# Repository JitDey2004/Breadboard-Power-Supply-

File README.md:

# Breadboard Power Supply

This project is a simple breadboard power supply PCB made in KiCad. It is designed to take a DC input supply and provide useful output rails for breadboard experiments.

The board includes a barrel jack input, an on/off slide switch, voltage regulators, output headers, screw terminals, and a power indicator LED. The schematic uses a 12 V input label, a fixed 5 V regulator, and an LM317 regulator set up for a 3.3 V output.

## What This Board Does

- Accepts power through a DC barrel jack.
- Uses a slide switch to turn the board on and off.
- Provides a regulated 5 V output using an LM7805 regulator.
- Provides a regulated 3.3 V output using an LM317 regulator.
- Breaks out power through pin headers and screw terminals.
- Shows power status with an LED indicator.

This kind of board is useful when testing small circuits on a breadboard. It lets you power logic circuits, sensors, microcontrollers, and other low-voltage modules from one compact PCB.

## Project Files

| File | Purpose |
| --- | --- |
| `Breadboard Power Supply.kicad_pro` | Main KiCad project file. Open this file in KiCad. |
| `Breadboard Power Supply.kicad_sch` | Schematic file. This shows the electrical circuit. |
| `Breadboard Power Supply.kicad_pcb` | PCB layout file. This shows the board routing and component placement. |
| `Breadboard Power Supply.kicad_prl` | KiCad local project settings file. |
| `0398800302.stp` | 3D model used by the PCB. |
| `500SSP1S1M2REA--3DModel-STEP-418109.STEP` | 3D model used by the PCB. |
| `img/` | Photos shown in this README. |
| `Breadboard Power Supply-backups/` | KiCad backup files. |

## Main Components

The schematic includes these main parts:

- `J1`: DC barrel jack input.
- `S1`: EG1218 slide switch.
- `U2`: LM7805 regulator for the 5 V rail.
- `U1`: LM317 regulator for the 3.3 V rail.
- `D1`: Power indicator LED.
- `R1`, `R2`, `R3`: Resistors for LED current limiting and regulator setting.
- `C1`, `C2`, `C3`: Capacitors for regulator stability and filtering.
- `J2`, `J5`: Screw terminal outputs.
- `J3`, `J4`, `J6`, `J7`: Pin header outputs.

## Power Notes

The input net is labelled as `12V` in the schematic. Use a DC supply that is suitable for the regulators and the parts installed on the board.

The LM7805 regulator creates the 5 V output. The LM317 regulator creates the 3.3 V output using the resistor values shown in the schematic.

Linear regulators can become hot when the input voltage is much higher than the output voltage or when the load current is high. Check the regulator temperature during testing. Add heatsinks if needed.

## How to Open the Project

1. Install KiCad.
2. Open KiCad.
3. Choose **File > Open Project**.
4. Select `Breadboard Power Supply.kicad_pro`.
5. Open the schematic or PCB layout from the KiCad project window.

## Before Making the PCB

Before sending the board for manufacturing, check the design carefully:

1. Run the Electrical Rules Checker in the schematic editor.
2. Run the Design Rules Checker in the PCB editor.
3. Confirm the footprints match the real parts you will use.
4. Check the pinout of the barrel jack, regulators, switch, headers, and screw terminals.
5. Inspect the 3D view to make sure the parts fit correctly.
6. Generate Gerber files only after the checks pass.

## Suggested Assembly Order

1. Solder the resistors first.
2. Solder the capacitors.
3. Solder the LED.
4. Solder the pin headers and screw terminals.
5. Solder the barrel jack and slide switch.
6. Solder the voltage regulators last.
7. Inspect all solder joints before applying power.

## First Power Test

Use a current-limited power supply for the first test if possible.

1. Keep the board disconnected from any breadboard circuit.
2. Apply the input voltage.
3. Turn the slide switch on.
4. Check that the power LED turns on.
5. Measure the 5 V output with a multimeter.
6. Measure the 3.3 V output with a multimeter.
7. Turn the board off and check that the outputs turn off.

Do not connect sensitive parts until the output voltages are confirmed.

## Safety

This board is intended for low-voltage electronics experiments. Do not connect it directly to mains voltage. Always check polarity before applying power.

## Author

Designed by Jit Dey.

## Project Images

These photos show the breadboard power supply project.

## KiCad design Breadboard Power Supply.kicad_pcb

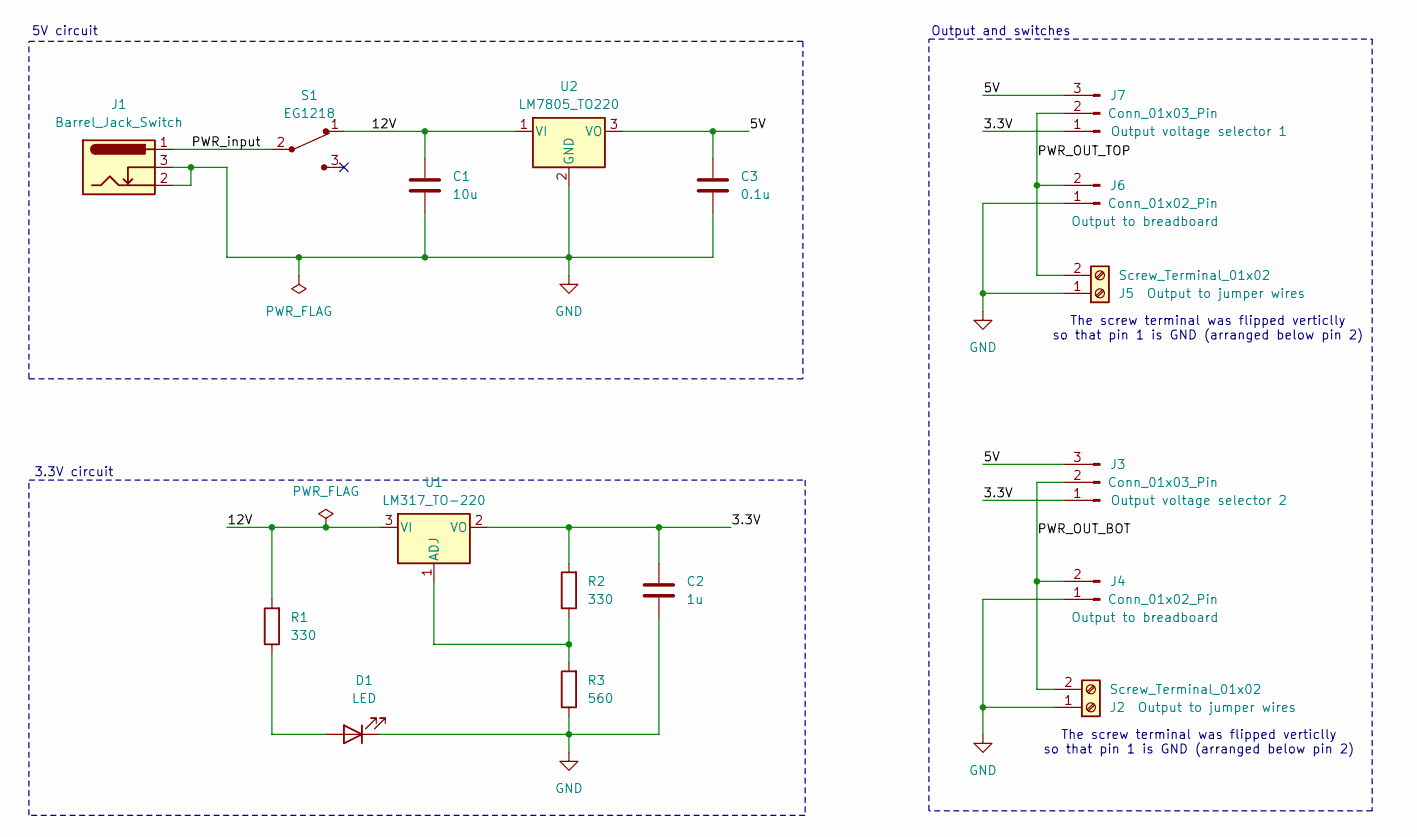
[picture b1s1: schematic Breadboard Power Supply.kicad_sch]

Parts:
C1: 10u; C_Disc_D3.0mm_W1.6mm_P2.50mm
C2: 1u; C_Disc_D3.0mm_W1.6mm_P2.50mm
C3: 0.1u; C_Disc_D3.0mm_W1.6mm_P2.50mm
D1: LED; LED_D5.0mm
J1: Barrel_Jack_Switch; BarrelJack_Horizontal
J2, J5: Screw_Terminal_01x02; TerminalBlock_bornier-2_P5.08mm
J3, J7: Conn_01x03_Pin; PinHeader_1x03_P2.54mm_Vertical
J4, J6: Conn_01x02_Pin; PinHeader_1x02_P2.54mm_Vertical
R1, R2: 330; R_Axial_DIN0204_L3.6mm_D1.6mm_P7.62mm_Horizontal
R3: 560; R_Axial_DIN0204_L3.6mm_D1.6mm_P7.62mm_Horizontal
S1: EG1218; Switch_Slide_11.6x4mm_EG1218; MPN EG1218; Digi-Key_PN EG1903-ND
U1: LM317_TO-220; TO-220-3_Vertical
U2: LM7805_TO220; TO-220-3_Vertical

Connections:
/3.3V: C2.1, J3.1, J7.1, R2.2, U1.2 (VO)
/5V: C3.1, J3.3, J7.3, U2.3 (VO)
/12V: C1.1, R1.2, S1.1, U1.3 (VI), U2.1 (VI)
/PWR_OUT_BOT: J2.2, J3.2, J4.2
/PWR_OUT_TOP: J5.2, J6.2, J7.2
/PWR_input: J1.1, S1.2
GND: C1.2, C2.2, C3.2, D1.1 (K), J1.2, J1.3, J2.1, J4.1, J5.1, J6.1, R3.1, U2.2 (GND)
unnamed: D1.2 (A), R1.1
unnamed: R2.1, R3.2, U1.1 (ADJ)

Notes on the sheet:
3.3V circuit
5V circuit
Output and switches
The screw terminal was flipped verticlly so that pin 1 is GND (arranged below pin 2)

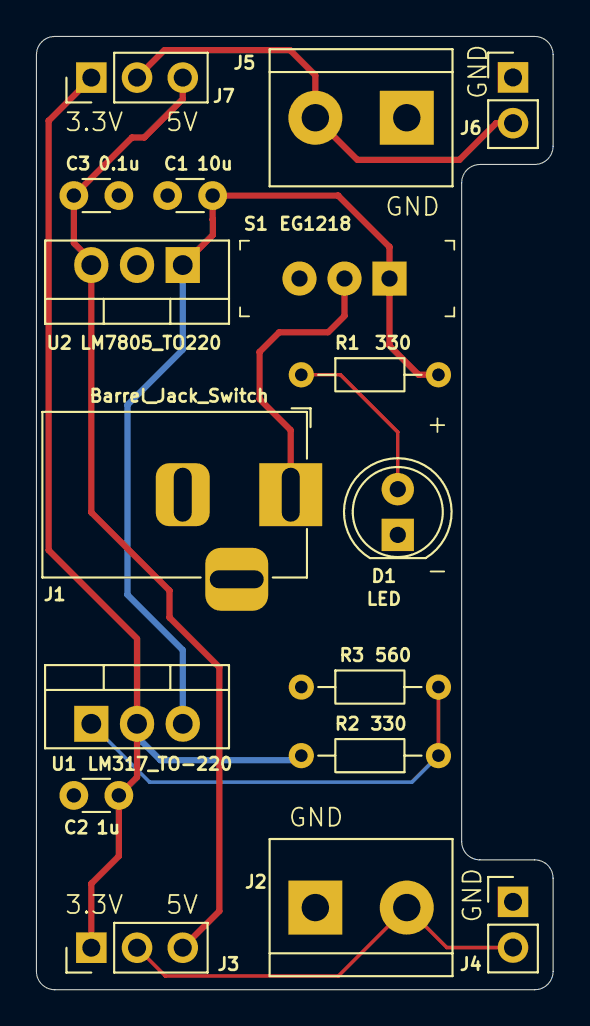
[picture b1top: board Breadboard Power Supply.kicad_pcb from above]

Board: 2 copper layers, 28.7 x 53.0 mm, 17 parts (0 on the bottom side), 9 nets.

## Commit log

2025-09-29 Add files via upload
    add the required files
